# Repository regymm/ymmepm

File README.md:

## YMMEPM

#### CPLD Dev Board & Handheld Serial Terminal

Board with Altera MAX II EPM1270. With a pluggable 480x320 LCD screen and a matrix keyboard, it work well as a handheld serial terminal. [Video](https://t.me/petergulife/174). 

**Gallery**

**The terminal**

`rtl/lcd_terminal.v`

Due to the scares resource of the EPM1270, the terminal supports only basic cursor movement and clear VT100(`^[[X`) sequences, others are detected and ignored. Have to put character pixel lists into slow UFM, so only up to 19200 baud rate. In case of Linux, bash and commands like `ls` work. `nano` won't display correctly and the editor that works is `ed` or my [ymedit](https://github.com/regymm/ymedit). CTS flow control is utilized to avoid losing chars when clearing full screen. (so need to connect 5 wires to use: 5V0, GND, rx, tx, cts)

**The keyboard**

`rtl/uart_keyboard.v`

Currently support only single-byte chars, arrow keys won't work. In code UP and RIGHT are used as extra SHIFT and CTRL. 

Covering keyboard with high-temperature yellow tape will significantly improve type feeling. 

**Design**

Simple is the main concern ... or not?

Single 3V3, or single 5V0 with ASM1117 to 3V3. 

Right two PMODs directly connected to CPLD. Left 2 PMODs share the Arduino pins(these literally give the plugged LCD screen a PMOD interface). Spare IOs scattered here and there. 

1 power LED, 2 user LEDs, 2 user jumpers. 2 oscillators. A strange matrix keyboard. 

For the simplest verification, only the CPLD, power pins, and JTAG pins are needed. Even caps on the back can be left empty. 

Footprint is compatible with EPM1270/570/240 TQFP144/100, but certainly the full terminal can only fit into EPM1270(~ 90% logic elements used). 

**Bugs**

5V is not connected to the Arduino pin. Fly a wire from ASM1117 if using 5V LCD screen. 

JTAG header pins should be soldered on back of the board. 

Still some tiny problems in the supported VT100 controls. But if the fix is paid in extra logic elements, I have to consider.

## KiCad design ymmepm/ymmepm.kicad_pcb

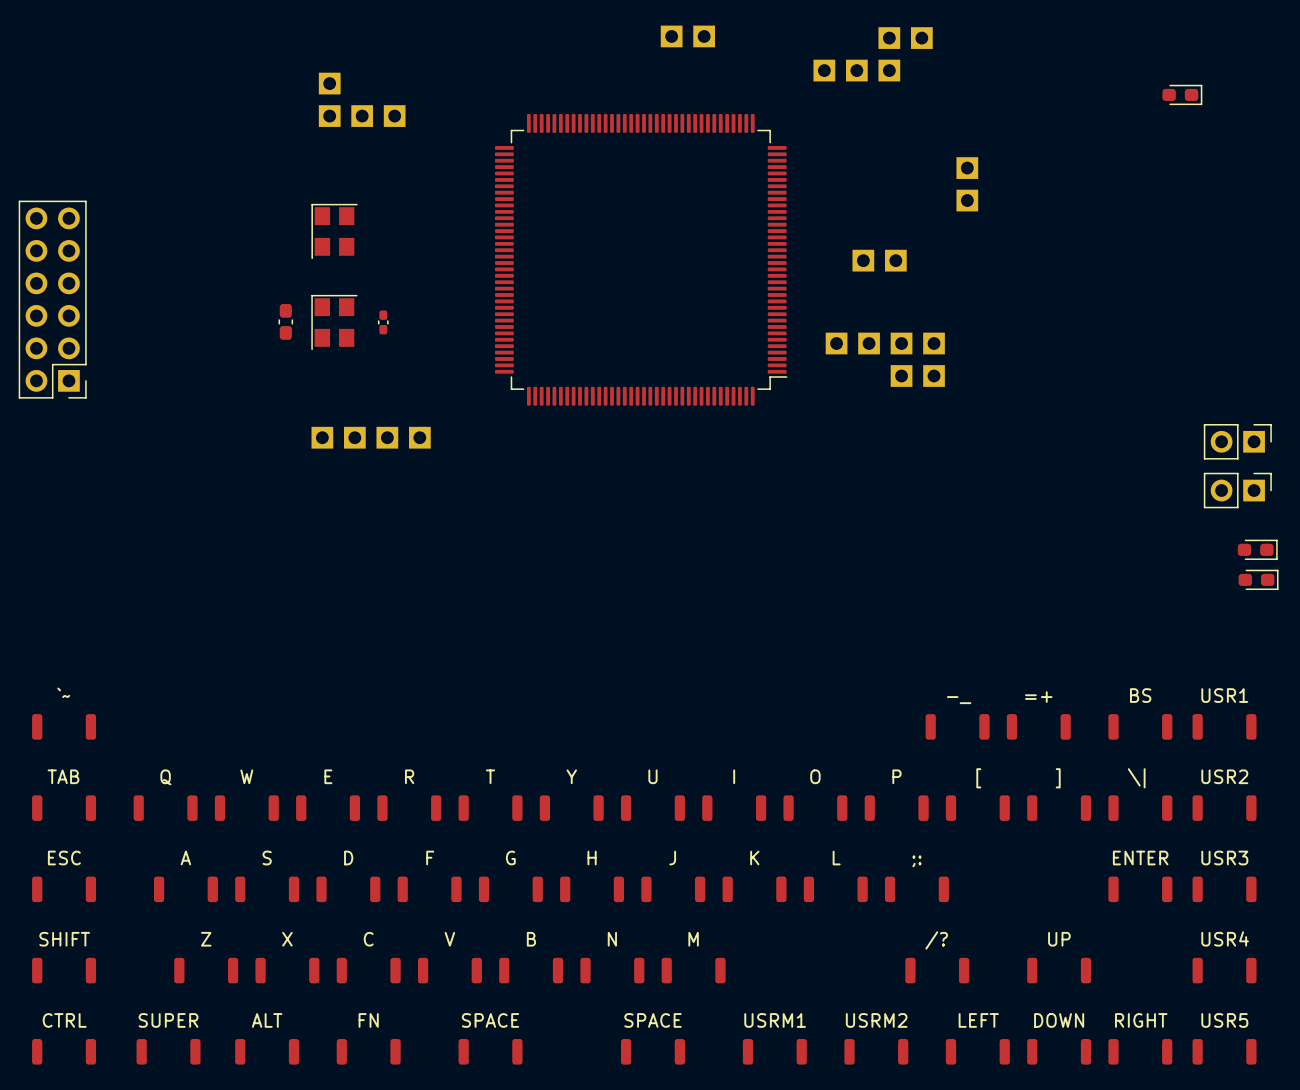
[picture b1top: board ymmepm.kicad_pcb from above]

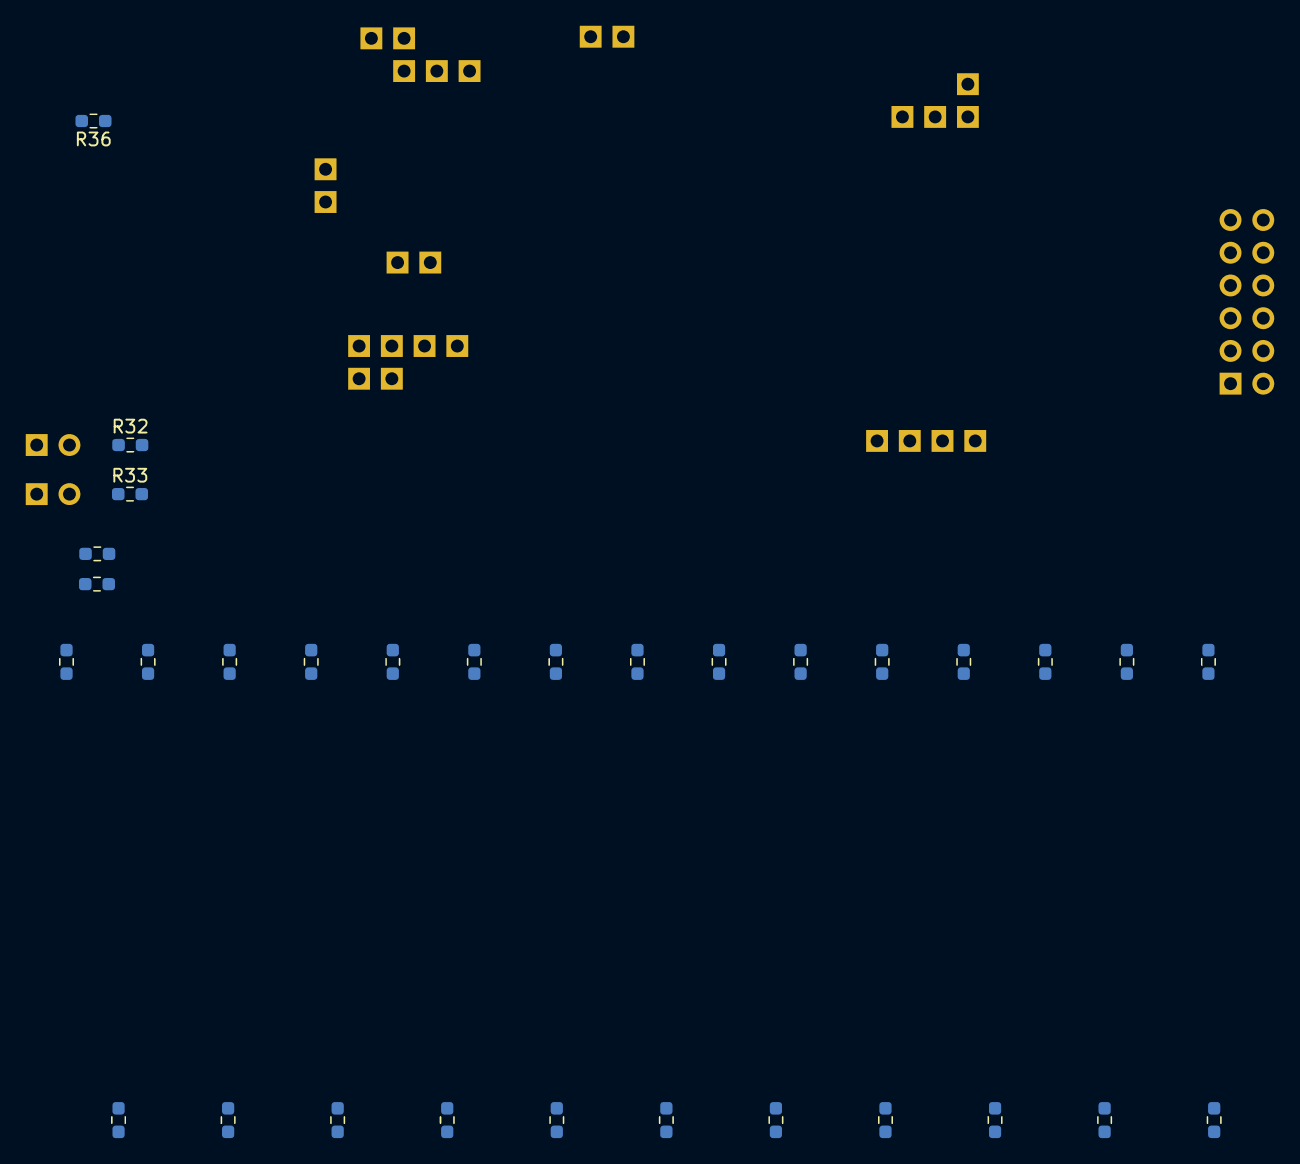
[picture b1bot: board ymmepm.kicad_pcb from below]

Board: 2 copper layers, 124 parts (31 on the bottom side), 76 nets, no tracks yet.

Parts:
'1: KEY; SW_Push_SPST_NO_Alps_SKRK_BARE
-1: KEY; SW_Push_SPST_NO_Alps_SKRK_BARE
/1: KEY; SW_Push_SPST_NO_Alps_SKRK_BARE
;1: KEY; SW_Push_SPST_NO_Alps_SKRK_BARE
=1: KEY; SW_Push_SPST_NO_Alps_SKRK_BARE
A1: KEY; SW_Push_SPST_NO_Alps_SKRK_BARE
AD1: KEY; SW_Push_SPST_NO_Alps_SKRK_BARE
AL1: KEY; SW_Push_SPST_NO_Alps_SKRK_BARE
ALT1: KEY; SW_Push_SPST_NO_Alps_SKRK_BARE
AR1: KEY; SW_Push_SPST_NO_Alps_SKRK_BARE
AU1: KEY; SW_Push_SPST_NO_Alps_SKRK_BARE
B1: KEY; SW_Push_SPST_NO_Alps_SKRK_BARE
BS1: KEY; SW_Push_SPST_NO_Alps_SKRK_BARE
C17: KEY; SW_Push_SPST_NO_Alps_SKRK_BARE
C18: C; C_0603_1608Metric_Pad1.08x0.95mm_HandSolder
C19: C0402; C_0402_1005Metric_Pad0.74x0.62mm_HandSolder
CTRL1: KEY; SW_Push_SPST_NO_Alps_SKRK_BARE
D1: KEY; SW_Push_SPST_NO_Alps_SKRK_BARE
D2, D3, D4: LED; LED_0603_1608Metric_Pad1.05x0.95mm_HandSolder
E1: KEY; SW_Push_SPST_NO_Alps_SKRK_BARE
ESC1: KEY; SW_Push_SPST_NO_Alps_SKRK_BARE
ETR1: KEY; SW_Push_SPST_NO_Alps_SKRK_BARE
F1: KEY; SW_Push_SPST_NO_Alps_SKRK_BARE
FN1: KEY; SW_Push_SPST_NO_Alps_SKRK_BARE
G1: KEY; SW_Push_SPST_NO_Alps_SKRK_BARE
H1: KEY; SW_Push_SPST_NO_Alps_SKRK_BARE
I1: KEY; SW_Push_SPST_NO_Alps_SKRK_BARE
J11: KEY; SW_Push_SPST_NO_Alps_SKRK_BARE
J13: JP1; PinHeader_1x02_P2.54mm_Vertical
J14: JP2; PinHeader_1x02_P2.54mm_Vertical
J15: PMOD1; PinHeader_2x06_P2.54mm_Vertical
J16, J17, J18, J19, J20, J21, J22, J23, J24, J25, J26, J27, J28, J29, J30, J31, J32, J33, J34, J35, J36, J37, J38, J39, J40: HOLE; PinHeader_1x01_P2.54mm_Vertical_BARE
K1: KEY; SW_Push_SPST_NO_Alps_SKRK_BARE
L1: KEY; SW_Push_SPST_NO_Alps_SKRK_BARE
M1: KEY; SW_Push_SPST_NO_Alps_SKRK_BARE
N1: KEY; SW_Push_SPST_NO_Alps_SKRK_BARE
O1: KEY; SW_Push_SPST_NO_Alps_SKRK_BARE
P1: KEY; SW_Push_SPST_NO_Alps_SKRK_BARE
Q1: KEY; SW_Push_SPST_NO_Alps_SKRK_BARE
R5: KEY; SW_Push_SPST_NO_Alps_SKRK_BARE
R6, R7, R8, R9, R10, R11, R12, R13, R14, R15, R16, R17, R18, R19, R20, R21, R22, R23, R24, R25, R26, R27, R28, R29, R30, R31, R32, R33, R34, R35, R36: R; R_0603_1608Metric_Pad0.98x0.95mm_HandSolder
S1: KEY; SW_Push_SPST_NO_Alps_SKRK_BARE
SHIFT1: KEY; SW_Push_SPST_NO_Alps_SKRK_BARE
SP1, SP2: KEY; SW_Push_SPST_NO_Alps_SKRK_BARE
SUPER1: KEY; SW_Push_SPST_NO_Alps_SKRK_BARE
T1: KEY; SW_Push_SPST_NO_Alps_SKRK_BARE
TAB1: KEY; SW_Push_SPST_NO_Alps_SKRK_BARE
U1: EPM1270T144; LQFP-144_20x20mm_P0.5mm
U3: KEY; SW_Push_SPST_NO_Alps_SKRK_BARE
USR1, USR2, USR3, USR4, USR5: KEY; SW_Push_SPST_NO_Alps_SKRK_BARE
USRM1, USRM2: KEY; SW_Push_SPST_NO_Alps_SKRK_BARE
V1: KEY; SW_Push_SPST_NO_Alps_SKRK_BARE
W1: KEY; SW_Push_SPST_NO_Alps_SKRK_BARE
X1, X3: Just an OSC; Oscillator_SMD_SeikoEpson_SG8002CE-4Pin_3.2x2.5mm
X2: KEY; SW_Push_SPST_NO_Alps_SKRK_BARE
Y1: KEY; SW_Push_SPST_NO_Alps_SKRK_BARE
Z1: KEY; SW_Push_SPST_NO_Alps_SKRK_BARE
[1: KEY; SW_Push_SPST_NO_Alps_SKRK_BARE
\1: KEY; SW_Push_SPST_NO_Alps_SKRK_BARE
]1: KEY; SW_Push_SPST_NO_Alps_SKRK_BARE
`1: KEY; SW_Push_SPST_NO_Alps_SKRK_BARE

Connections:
+3V3: C18.1, C19.1, J13.1, J14.1, J15.1, J15.2, R6.1, R7.1, R8.1, R9.1, R10.1, R11.1, R12.1, R13.1, R14.1, R15.1, R16.1, R17.1, R18.1, R19.1, R20.1, R21.1, R22.1, R23.1, R24.1, R25.1, R26.1, R27.1, R28.1, R29.1, R30.1, R31.1, R36.2, U1.9, U1.19, U1.25, U1.46, U1.56, U1.64, U1.82, U1.90, U1.100, U1.116, U1.126, U1.136, X1.4, X3.4
/IO1: J30.1, U1.1
/IO2: J29.1, U1.2
/IO3: J28.1, U1.3
/IO4: J23.1, U1.4
/IO5: CTRL1.2, R13.2, U1.5
/IO6: R11.2, SHIFT1.2, U1.6
/IO7: R35.2, U1.7
/IO8: R34.2, U1.8
/IO11: J14.2, R33.1, U1.11
/IO12: J13.2, R32.1, U1.12
/IO15: J21.1, U1.15
/IO16: J22.1, U1.16
/IO27: J27.1, U1.27
/IO28: J26.1, U1.28
/IO29: J25.1, U1.29
/IO30: J24.1, U1.30
/IO31: J20.1, U1.31
/IO32: J19.1, U1.32
/IO37: J18.1, U1.37
/IO48: J16.1, U1.48
/IO49: J17.1, U1.49
/IO73: SP1.1, SP2.1, U1.73, USR5.1
/IO74: /1.1, B1.1, C17.1, ESC1.1, M1.1, N1.1, U1.74, USR4.1, V1.1, X2.1, Z1.1
/IO75: ;1.1, A1.1, D1.1, ETR1.1, F1.1, G1.1, H1.1, J11.1, K1.1, L1.1, S1.1, TAB1.1, U1.75, USR3.1
/IO76: E1.1, I1.1, O1.1, P1.1, Q1.1, R5.1, T1.1, U1.76, U3.1, USR2.1, W1.1, Y1.1, [1.1, \1.1, ]1.1, `1.1
/IO77: -1.1, =1.1, BS1.1, U1.77, USR1.1
/IO78: J15.12, U1.78
/IO79: J15.11, U1.79
/IO80: J15.10, U1.80
/IO81: ESC1.2, R6.2, TAB1.2, U1.81, `1.2
/IO84: J37.1, U1.84
/IO85: J38.1, U1.85
/IO86: J39.1, U1.86
/IO87: J40.1, U1.87
/IO88: A1.2, Q1.2, R7.2, U1.88, Z1.2
/IO89: U1.89, X1.3
/IO91: U1.91, X3.3
/IO93: R8.2, S1.2, U1.93, W1.2, X2.2
/IO94: C17.2, D1.2, E1.2, R9.2, U1.94
/IO95: F1.2, R5.2, R10.2, SP1.2, SP2.2, U1.95, V1.2
/IO96: B1.2, G1.2, R12.2, T1.2, U1.96
/IO97: H1.2, N1.2, R14.2, U1.97, Y1.2
/IO98: J11.2, M1.2, R16.2, U1.98, U3.2
/IO101: I1.2, K1.2, R18.2, U1.101
/IO102: L1.2, O1.2, R20.2, U1.102
/IO103: /1.2, ;1.2, P1.2, R22.2, U1.103
/IO104: -1.2, R24.2, U1.104, [1.2
/IO105: =1.2, ETR1.2, R26.2, U1.105, ]1.2
/IO106: J33.1, U1.106
/IO107: J34.1, U1.107
/IO108: J35.1, U1.108
/IO109: J36.1, U1.109
/IO112: J15.6, U1.112
/IO113: J15.5, U1.113
/IO114: J15.8, U1.114
/IO119: J15.7, U1.119
/IO120: J15.9, U1.120
/IO122: BS1.2, R28.2, U1.122, \1.2
/IO123: R30.2, U1.123, USR1.2, USR2.2, USR3.2, USR4.2, USR5.2
/IO124: AD1.1, AL1.1, ALT1.1, AR1.1, AU1.1, CTRL1.1, FN1.1, SHIFT1.1, SUPER1.1, U1.124, USRM1.1, USRM2.1
/IO125: AR1.2, R27.2, U1.125
/IO127: AD1.2, R25.2, U1.127
/IO129: AU1.2, R23.2, U1.129
/IO137: AL1.2, R21.2, U1.137
/IO138: R31.2, U1.138, USRM2.2
/IO139: R29.2, U1.139, USRM1.2
/IO140: FN1.2, R19.2, U1.140
/IO141: ALT1.2, R17.2, U1.141
/IO142: R15.2, SUPER1.2, U1.142
/IO143: J31.1, U1.143
/IO144: J32.1, U1.144
GND: C18.2, C19.2, D2.1, D3.1, D4.1, J15.3, J15.4, R32.2, R33.2, U1.10, U1.17, U1.26, U1.47, U1.54, U1.65, U1.83, U1.92, U1.99, U1.115, U1.128, U1.135, X1.2, X3.2
unnamed: D2.2, R34.1
unnamed: D3.2, R35.1
unnamed: D4.2, R36.1

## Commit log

2021-08-06 Start working on epm board
2021-08-07 Create LICENSE
2021-08-08 Continue
2021-08-08 Near close I think
2021-08-09 Go production at JLC purple
2021-08-14 Added some design files
2021-08-20 keyboard scanning basically works
2021-08-21 working on lcd terminal
2021-08-24 Combined keyboard and lcd, using UFM. Coding part seems done.
2021-08-25 Added more VT100 controls, added CTS
2021-08-26 V1.0
2021-08-26 Added pics
